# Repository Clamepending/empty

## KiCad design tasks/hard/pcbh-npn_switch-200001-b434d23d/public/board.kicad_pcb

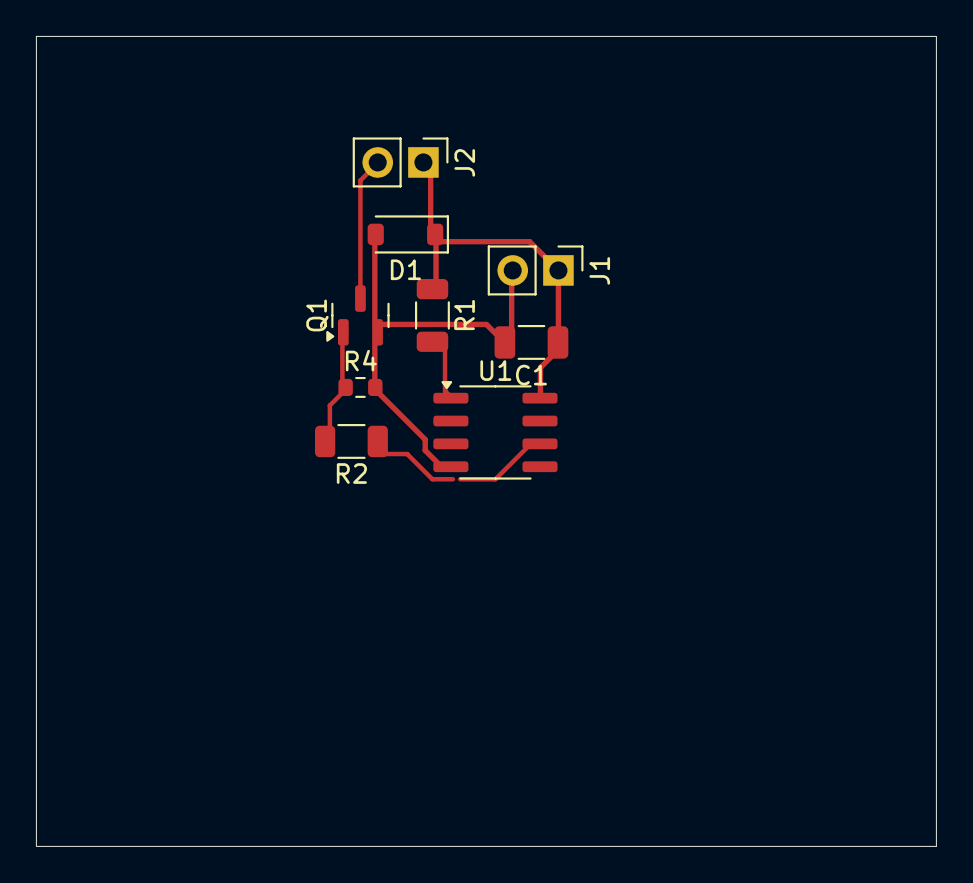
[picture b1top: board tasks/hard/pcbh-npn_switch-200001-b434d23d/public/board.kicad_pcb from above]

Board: 2 copper layers, 50.0 x 45.0 mm, 9 parts (0 on the bottom side), 6 nets.

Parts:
C1: 100n; C_1206_3216Metric
D1: D_SOD-123
J1, J2: PinHeader_1x02_P2.54mm_Vertical
Q1: SOT-23
R1: 30k; R_1206_3216Metric
R2: 1.2k; R_1206_3216Metric
R4: 91k; R_0603_1608Metric
U1: SOIC-8_3.9x4.9mm_P1.27mm

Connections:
+5V: C1.1, D1.1, J1.1, J2.1, R1.1, U1.8
BASE: Q1.1, R2.2, R4.1
CTRL: R2.1, U1.6
GND: C1.2, D1.2, J1.2, Q1.2, R4.2, U1.4
NRST: R1.2, U1.1
SW: J2.2, Q1.3

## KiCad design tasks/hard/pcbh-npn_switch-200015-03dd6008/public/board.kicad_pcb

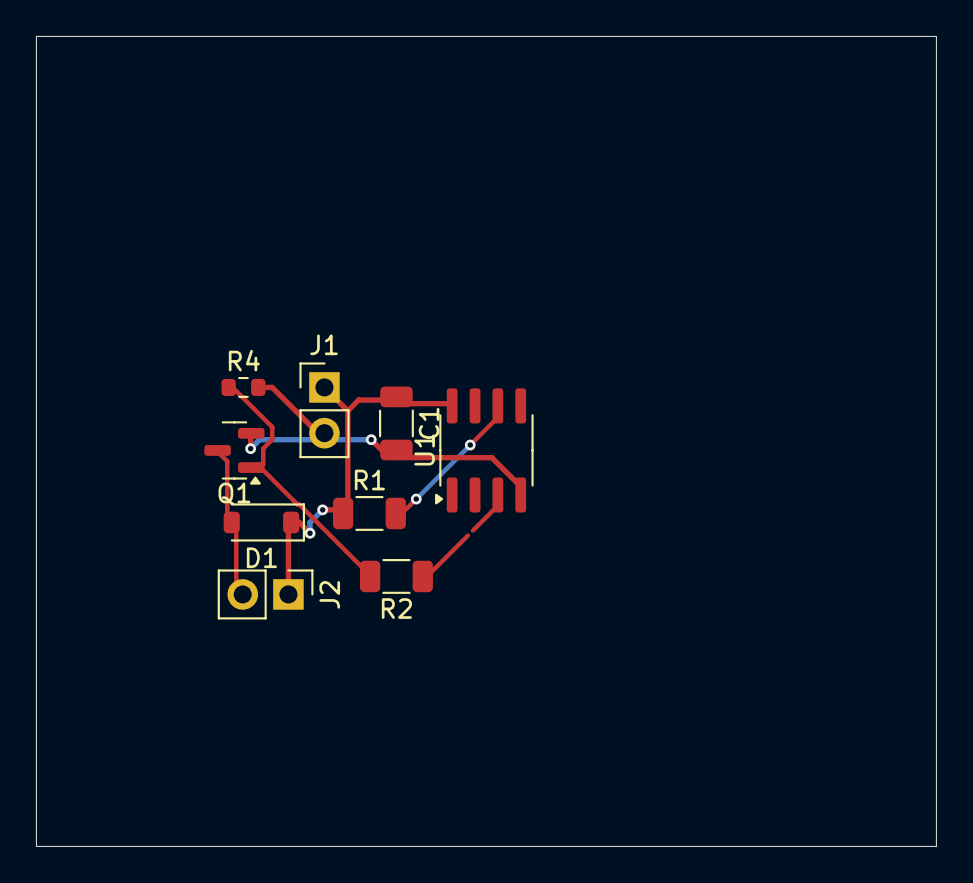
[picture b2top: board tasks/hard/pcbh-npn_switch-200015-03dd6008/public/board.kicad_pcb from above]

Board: 2 copper layers, 50.0 x 45.0 mm, 9 parts (0 on the bottom side), 6 nets.

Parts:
C1: 100n; C_1206_3216Metric
D1: D_SOD-123
J1, J2: PinHeader_1x02_P2.54mm_Vertical
Q1: SOT-23
R1: 27k; R_1206_3216Metric
R2: 3.2k; R_1206_3216Metric
R4: 30k; R_0603_1608Metric
U1: SOIC-8_3.9x4.9mm_P1.27mm

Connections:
+5V: C1.1, D1.1, J1.1, J2.1, R1.1, U1.8
BASE: Q1.1, R2.2, R4.1
CTRL: R2.1, U1.3
GND: C1.2, J1.2, Q1.2, R4.2, U1.4
NRST: R1.2, U1.6
SW: D1.2, J2.2, Q1.3

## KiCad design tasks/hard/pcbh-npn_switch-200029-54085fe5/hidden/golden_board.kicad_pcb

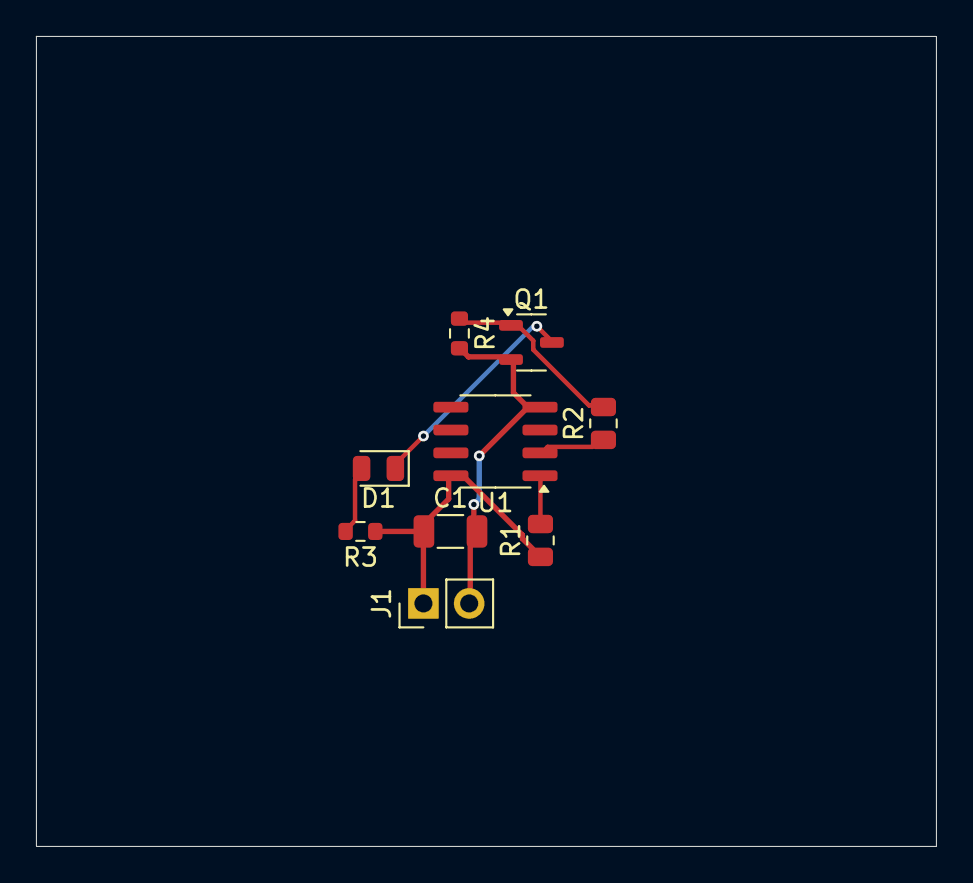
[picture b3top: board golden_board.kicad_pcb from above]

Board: 2 copper layers, 50.0 x 45.0 mm, 9 parts (0 on the bottom side), 7 nets.

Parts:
C1: 1u; C_1206_3216Metric
D1: LED_0805_2012Metric
J1: PinHeader_1x02_P2.54mm_Vertical
Q1: SOT-23-3
R1: 33k; R_0805_2012Metric
R2: 2.7k; R_0805_2012Metric
R3: 200; R_0603_1608Metric
R4: 24k; R_0603_1608Metric
U1: SOIC-8_3.9x4.9mm_P1.27mm

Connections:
+5V: C1.1, J1.1, R1.1, R3.1, U1.8
BASE: Q1.1, R2.2, R4.1
CTRL: R2.1, U1.2
GND: C1.2, J1.2, Q1.2, R4.2, U1.4
LED_A: D1.2, R3.2
NRST: R1.2, U1.1
SW: D1.1, Q1.3

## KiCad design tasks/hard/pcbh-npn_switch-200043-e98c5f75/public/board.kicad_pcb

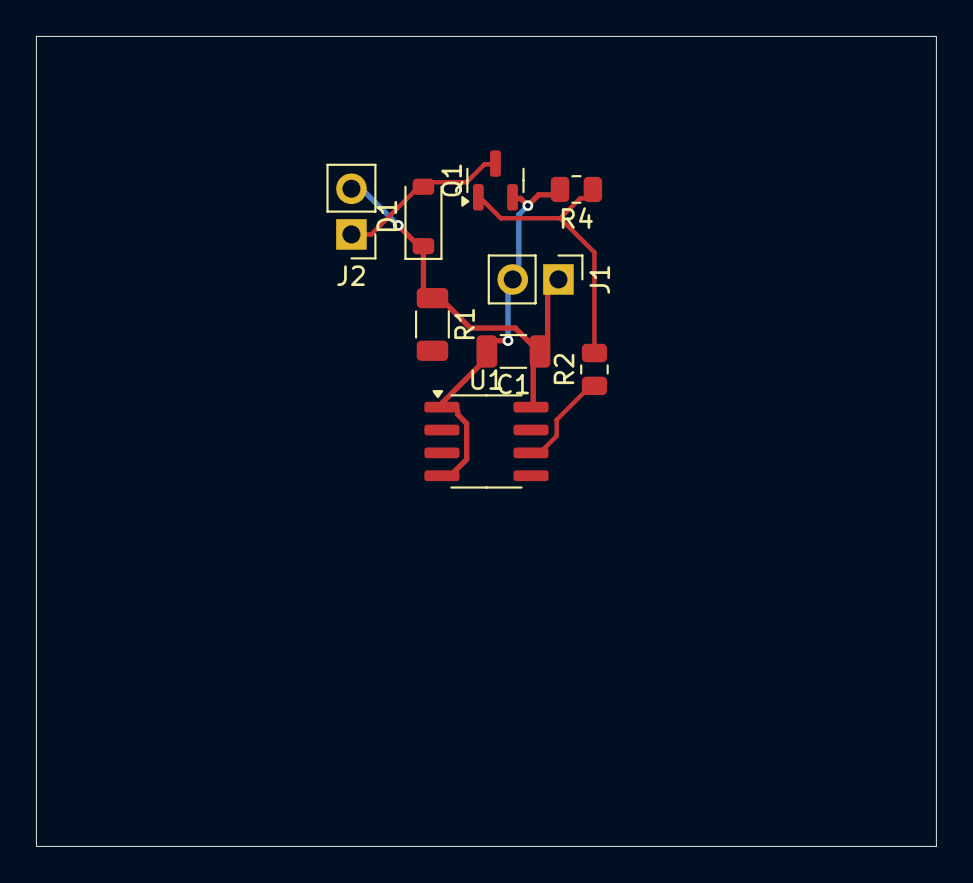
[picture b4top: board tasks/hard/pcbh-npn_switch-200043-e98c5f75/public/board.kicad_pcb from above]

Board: 2 copper layers, 50.0 x 45.0 mm, 9 parts (0 on the bottom side), 5 nets.

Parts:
C1: 100n; C_1206_3216Metric
D1: D_SOD-123
J1, J2: PinHeader_1x02_P2.54mm_Vertical
Q1: SOT-23
R1: 11k; R_1206_3216Metric
R2: 1.2k; R_0805_2012Metric
R4: 62k; R_0805_2012Metric
U1: SOIC-8_3.9x4.9mm_P1.27mm

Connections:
+5V: C1.1, D1.1, J1.1, J2.2, R1.1, U1.8
BASE: Q1.1, R2.2, R4.1
CTRL: R2.1, U1.6
GND: C1.2, J1.2, Q1.2, R4.2, U1.1, U1.4
SW: D1.2, J2.1, Q1.3
